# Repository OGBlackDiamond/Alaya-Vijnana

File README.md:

# Alaya-Vijnana
A wireless split ortholinear column-staggered keyboard that uses the Framework keyboard control board.

This is an adaptation of [Alaya-Vijnana-v2](https://github.com/OGBlackDiamond/Alaya-Vijnana-v2) to use Framework's wireless keyboard hardware, made under their developer program.

## What's an Alaya Vijnana?
The Alaya Vijnana system is a control interface to connect a Gundam pilot to their machine. I'm a nerd, and I name all of my computers after mobile suits (usually Gundams). Since a keyboard is how I interface with my computer, I felt a Gundam control system was an apt name.

For more information, visit [the IBO wiki](https://g-tekketsu.fandom.com/wiki/Alaya-Vijnana_System).

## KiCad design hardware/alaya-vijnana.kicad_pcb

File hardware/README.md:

# Alaya Vijnana Hardware

## B.O.M.
This is a complete B.O.M. for one half of the Alaya Vijnana's PCB components.

MCU:
* nRF52840 - [aQFN73](https://mm.digikey.com/Volume0/opasdata/d220001/medias/docus/6470/NRF52840-QFAA-F-R7.pdf)

Crystal Oscillators:
* 32MHz - [ECX-35B](https://ecsxtal.com/store/pdf/ecx_53b.pdf)
* 32.768kHz - [CM2012H](https://cfd.citizen.co.jp/cms/cfd/pdf/english/CM2012H_E.pdf)

Charger and Power:
* Charger - [BQ24075RGTR](https://www.digikey.com/en/products/detail/texas-instruments/BQ24075RGTR/2047273)
* Voltage Reg - [XC6220B331MR-G](https://www.digikey.com/en/products/detail/torex-semiconductor-ltd/XC6220B331MR-G/2138177?s=N4IgTCBcDaIB4GMBsYwAYBGBmLBGAtgE4gC6AvkA)

Battery Connector:
* JST PH - [S2B-PH-K-S](https://www.digikey.com/en/products/detail/jst-sales-america-inc/S2B-PH-K-S/926626)

Main to Cluster:
* 02x03 Header - 2 - [BHR-06-HUA](https://www.digikey.com/en/products/detail/adam-tech/BHR-06-HUA/10414833)
* Cable - 1 - [371](https://www.digikey.com/en/products/detail/adafruit-industries-llc/371/6827038)

Power Switch:
* E-Switch - [EG1224](https://www.digikey.com/en/products/detail/e-switch/EG1224/502052?s=N4IgTCBcDaIKIHEAEBGMYAsIC6BfIA)

USB-C Connector:
* USB CONN - [USB4085-GF-A](https://www.digikey.com/en/products/detail/gct/USB4085-GF-A/9859662?s=N4IgTCBcDaIKoGUBCAWADADgKwFoDiAYjgIIgC6AvkA)

Inductors:
* 10uH - 2 - [MLZ1608M100WTD25](https://www.digikey.com/en/products/detail/tdk-corporation/MLZ1608M100WTD25/4743176)
* 15nH - 1 - [LRC0603CJ15NGV001T](https://www.digikey.com/en/products/detail/johanson-technology-inc/LRC0603CJ15NGV001T/1561308)
* 4.7nH - 1 - [LRC0603CS4N7GV001T](https://www.digikey.com/en/products/detail/johanson-technology-inc/LRC0603CS4N7GV001T/1561296)

LEDs:
* Charge - 1 - [HSMD-C150](https://www.digikey.com/en/products/detail/broadcom-limited/HSMD-C150/637702)

Diodes:
* 21 - [CDSU101A](https://www.digikey.com/en/products/detail/comchip-technology/CDSU101A/1121034)

Hot Swap Sockets:
* 2 (1 = 20pc) - [4958](https://www.digikey.com/en/products/detail/adafruit-industries-llc/4958/13997772)

Resistors:
* 10k - 3 - [RC0603FR-0710KL](https://www.digikey.com/en/products/detail/yageo/RC0603FR-0710KL/726880)
* 10M - 1 - [RC0603JR-0710ML](https://www.digikey.com/en/products/detail/yageo/RC0603JR-0710ML/726701)
* 5.1k - 2 - [RC0603FR-075K1L](https://www.digikey.com/en/products/detail/yageo/RC0603FR-075K1L/727268)
* 2k - 1 - [RC0603JR-072KL](https://www.digikey.com/en/products/detail/yageo/RC0603JR-072KL/726726https://www.digikey.com/en/products/detail/yageo/RC0603JR-072KL/726726)

Capacitors:
* 12pF - 4 - [0603N120J500CT](https://www.digikey.com/en/products/detail/walsin-technology-corporation/0603N120J500CT/9355484)
* 1uF - 3 - [TMK107B7105KA-T](https://www.digikey.com/en/products/detail/taiyo-yuden/TMK107B7105KA-T/2714162)
* 4.7uF - 8 - [C1608X5R1C475K080AC](https://www.digikey.com/en/products/detail/tdk-corporation/C1608X5R1C475K080AC/2732913)
* 0.8pF - 1 - [CC0603BRNPO9BNR80](https://www.digikey.com/en/products/detail/yageo/CC0603BRNPO9BNR80/11490491)
* 0.5pF - 1 - [CBR06C508B5GAC](https://www.digikey.com/en/products/detail/kemet/CBR06C508B5GAC/3473906)
* 10uF - 1 - [LMK107BBJ106MALT](https://www.digikey.com/en/products/detail/taiyo-yuden/LMK107BBJ106MALT/3662195)
* 100pF - 2 - [CC0603JRNPO9BN101](https://www.digikey.com/en/products/detail/yageo/CC0603JRNPO9BN101/302803)
* 820pF - 1 - [CC0603KRX7R9BB821](https://www.digikey.com/en/products/detail/yageo/CC0603KRX7R9BB821/372862)
* 0.047uF - 1 - [CC0603KRX7R8BB473](https://www.digikey.com/en/products/detail/yageo/CC0603KRX7R8BB473/2103111)
* 0.1uF - 3 - [CC0603KRX7R7BB104](https://www.digikey.com/en/products/detail/yageo/CC0603KRX7R7BB104/302822)

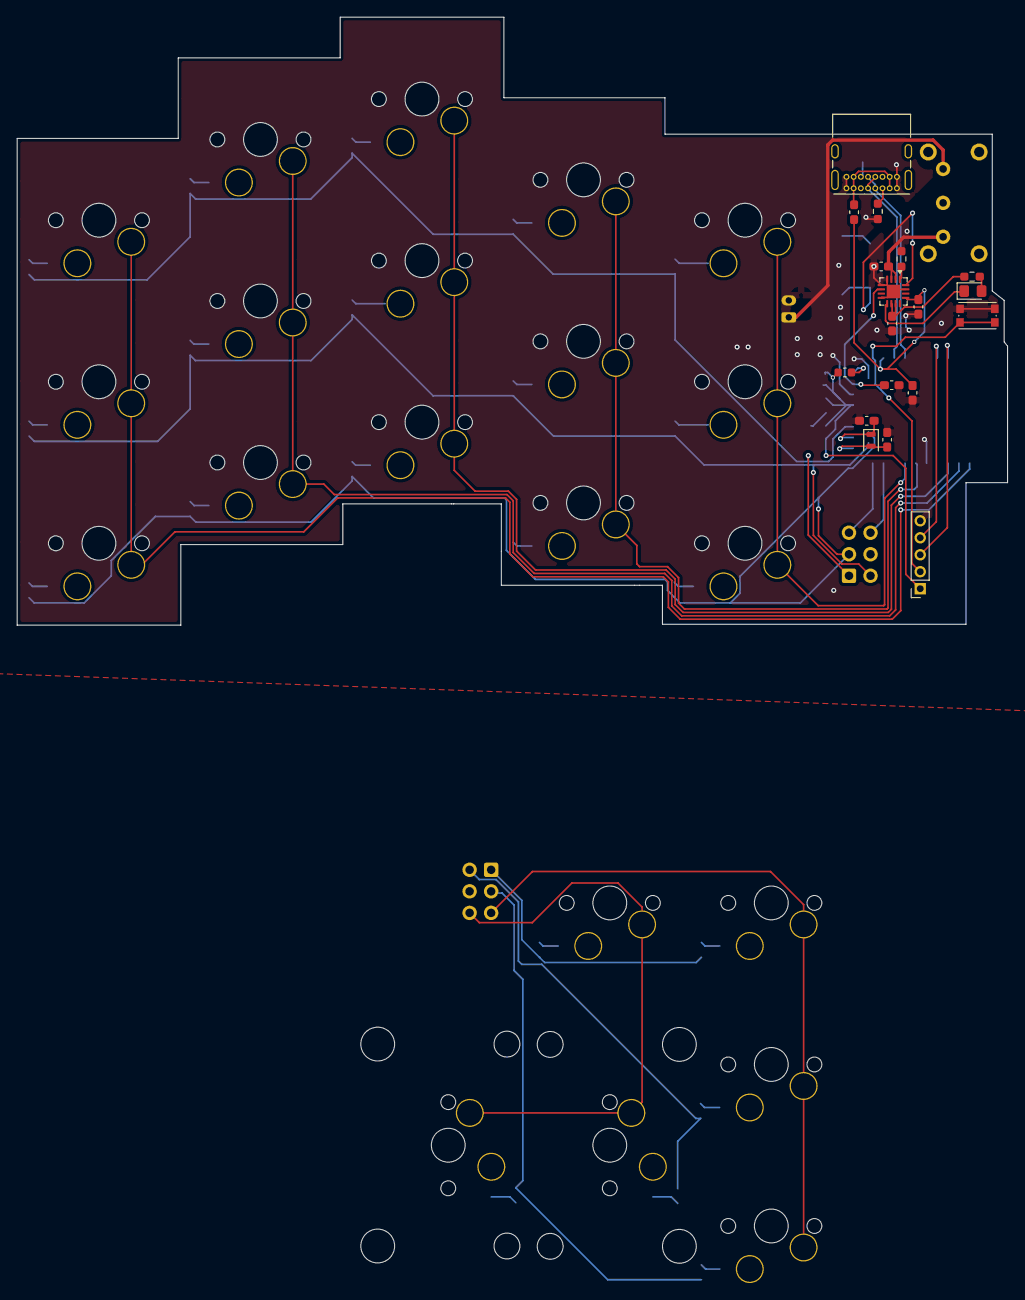
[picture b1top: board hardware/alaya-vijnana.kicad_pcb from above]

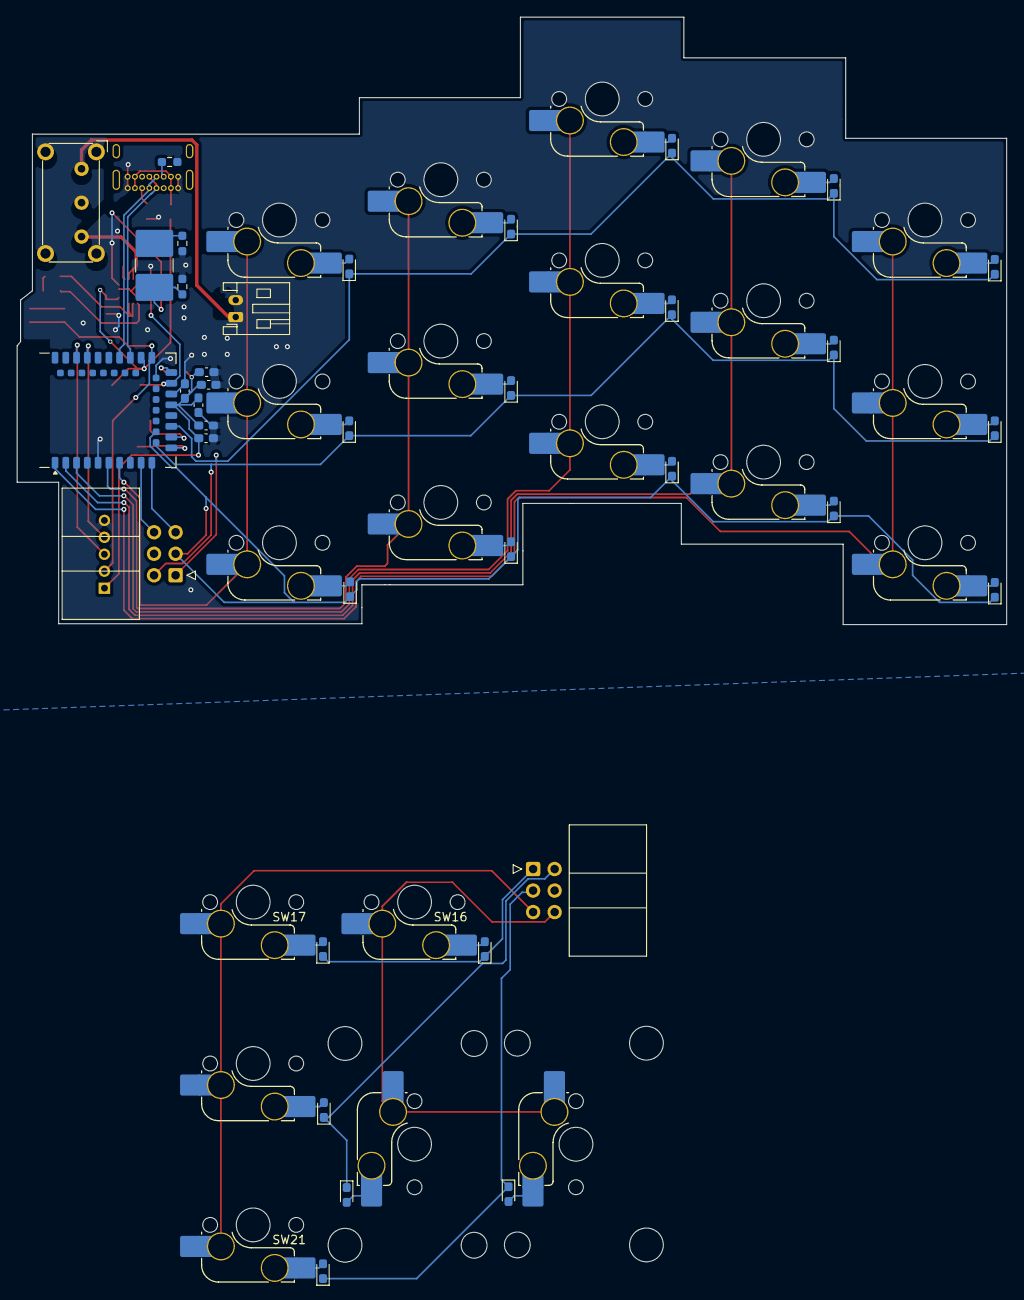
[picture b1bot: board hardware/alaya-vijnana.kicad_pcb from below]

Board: 2 copper layers, 116.8 x 71.7 mm, 75 parts (57 on the bottom side), 58 nets.

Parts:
C1, C30, C37, C46, C47: 4.7uF; C_0603_1608Metric_Pad1.08x0.95mm_HandSolder
C2: 1u; C_0603_1608Metric_Pad1.08x0.95mm_HandSolder
C26: 1uf; C_0603_1608Metric_Pad1.08x0.95mm_HandSolder
C27, C28, C29: 100nF; C_0603_1608Metric_Pad1.08x0.95mm_HandSolder
C41, C42: 12pF; C_0603_1608Metric_Pad1.08x0.95mm_HandSolder
C44: 1uF; C_0603_1608Metric_Pad1.08x0.95mm_HandSolder
D22, D23, D24, D25, D26, D27, D28, D29, D30, D31, D32, D33, D34, D35, D36, D37, D38, D39, D40, D41, D42: D; D_0603_1608Metric_Pad1.05x0.95mm_HandSolder
F1: 750 mA; Fuse_0603_1608Metric_Pad1.05x0.95mm_HandSolder
J1: Debug/Flash; PinSocket_1x05_P2.00mm_Vertical
J3: Bat; JST_PH_S2B-PH-K_1x02_P2.00mm_Horizontal
J4: USB_C_Receptacle_USB2.0_16P; USB_C_Receptacle_GCT_USB4085
J6: MAIN_CONN; IDC-Header_2x03_P2.54mm_Horizontal
J7: CLUSTER_CONN; IDC-Header_2x03_P2.54mm_Horizontal
L7: 10uH; L_0603_1608Metric
LED2: Charge_LED; LED_0805_2012Metric_Pad1.15x1.40mm_HandSolder
POWER-SW1: Power_Switch; SW_E-Switch_EG1224_SPDT_Angled
R8: 2k; R_0603_1608Metric_Pad0.98x0.95mm_HandSolder
R9, R11, R12: 10k; R_0603_1608Metric_Pad0.98x0.95mm_HandSolder
R13, R14: 5.1k; R_0603_1608Metric_Pad0.98x0.95mm_HandSolder
RESET-SW1: Reset; SW_Push_1P1T_NO_CK_KMR2
SW1, SW2, SW3, SW4, SW5, SW6, SW7, SW8, SW9, SW10, SW11, SW12, SW13, SW14, SW15, SW16, SW17, SW18, SW19, SW20, SW21: MX HotSwap; SW_MX_HS_CPG151101S11_1u
TP2: Charge Boost; R_2816_7142Metric_Pad3.20x4.45mm_HandSolder
U1: nRF52840_E73-2G4M08S1C
U6: BQ24075RGT; VQFN-16-1EP_3x3mm_P0.5mm_EP1.6x1.6mm
X2: 32.768kHz; Crystal_SMD_2012-2Pin_2.0x1.2mm

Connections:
BAT+: J3.1, POWER-SW1.1 (B)
BAT-: C1.1, C2.2, C26.2, C27.2, C28.2, C29.2, C30.2, C37.1, C41.1, C42.1, C44.1, C46.1, C47.2, J1.5, J3.2, J4.A1 (GND), J4.A12 (GND), J4.B1 (GND), J4.B12 (GND), R8.1, R9.2, R11.2, R13.2, R14.2, RESET-SW1.2, U1.5 (GND), U1.21 (GND), U1.24 (GND), U6.4 (~CE), U6.5 (EN2), U6.8 (VSS), U6.15 (SYSOFF), U6.17 (VSS)
COL0: SW1.1, SW6.1, SW11.1, U1.1 (P1.11)
COL1: SW2.1, SW7.1, SW12.1, U1.2 (P1.10)
COL2: SW3.1, SW8.1, SW13.1, U1.3 (P0.03/AIN1)
COL3: SW4.1, SW9.1, SW14.1, U1.6 (P1.13)
COL4: SW5.1, SW10.1, SW15.1, U1.7 (P0.02/AIN0)
COL5: J6.6, U1.9 (P0.31/AIN7)
COL6: J6.5, U1.10 (P0.30/AIN6)
C_COL5: J7.6, SW16.1, SW18.1, SW20.1
C_COL6: J7.5, SW17.1, SW19.1, SW21.1
C_ROW0: D37.1 (K), D40.1 (K), J7.1
C_ROW1: D38.1 (K), D41.1 (K), J7.2
C_ROW2: D39.1 (K), D42.1 (K), J7.3
D+: J4.A6 (D+), J4.B6 (D+), U1.31 (D+)
D-: J4.A7 (D-), J4.B7 (D-), U1.29 (D-)
unnamed: D22.2 (A), SW1.2
unnamed: D23.2 (A), SW6.2
unnamed: D24.2 (A), SW11.2
unnamed: D25.2 (A), SW2.2
unnamed: D26.2 (A), SW7.2
unnamed: D27.2 (A), SW12.2
unnamed: D28.2 (A), SW3.2
unnamed: D29.2 (A), SW8.2
unnamed: D30.2 (A), SW13.2
unnamed: D31.2 (A), SW4.2
unnamed: D32.2 (A), SW9.2
unnamed: D33.2 (A), SW14.2
unnamed: D34.2 (A), SW5.2
unnamed: D35.2 (A), SW10.2
unnamed: D36.2 (A), SW15.2
unnamed: D37.2 (A), SW16.2
unnamed: D38.2 (A), SW18.2
unnamed: D39.2 (A), SW20.2
unnamed: D40.2 (A), SW17.2
unnamed: D41.2 (A), SW19.2
unnamed: D42.2 (A), SW21.2
unnamed: F1.1, J4.A4 (VBUS), J4.A9 (VBUS), J4.B4 (VBUS), J4.B9 (VBUS)
unnamed: J4.A5 (CC1), R13.1
unnamed: J4.B5 (CC2), R14.1
unnamed: LED2.2 (A), R12.1
unnamed: LED2.1 (K), U6.9 (~CHG)
unnamed: R8.2, TP2.2
unnamed: L7.1, U1.25 (DCCH)
unnamed: C41.2, U1.11 (P0.00/XL1), X2.2
unnamed: C42.2, U1.13 (P0.01/XL2), X2.1
unnamed: R9.1, TP2.1, U6.16 (ISET)
unnamed: R11.1, U6.1 (TS)
RESET: J1.2, RESET-SW1.1, U1.26 (P0.18/~RESET)
ROW0: D22.1 (K), D25.1 (K), D28.1 (K), D31.1 (K), D34.1 (K), J6.1, U1.15 (P0.05/AIN3)
ROW1: D23.1 (K), D26.1 (K), D29.1 (K), D32.1 (K), D35.1 (K), J6.2, U1.12 (P0.26)
ROW2: D24.1 (K), D27.1 (K), D30.1 (K), D33.1 (K), D36.1 (K), J6.3, U1.14 (P0.06)
SWDCLK: J1.3, U1.39 (SWDCLK)
SWDIO: J1.4, U1.37 (SWDIO)
VBAT: C47.1, POWER-SW1.3 (A), U6.2 (BAT), U6.3 (BAT)
VBUS: C1.2, C44.2, F1.2, U1.27 (VBUS), U6.13 (IN)
VDDH: C37.2, C46.2, R12.2, U1.23 (VDDH), U6.6 (EN1), U6.10 (OUT), U6.11 (OUT)
VDD_NRF: C2.1, C26.1, C27.1, C28.1, C29.1, C30.1, J1.1, L7.2, U1.19 (VDD)

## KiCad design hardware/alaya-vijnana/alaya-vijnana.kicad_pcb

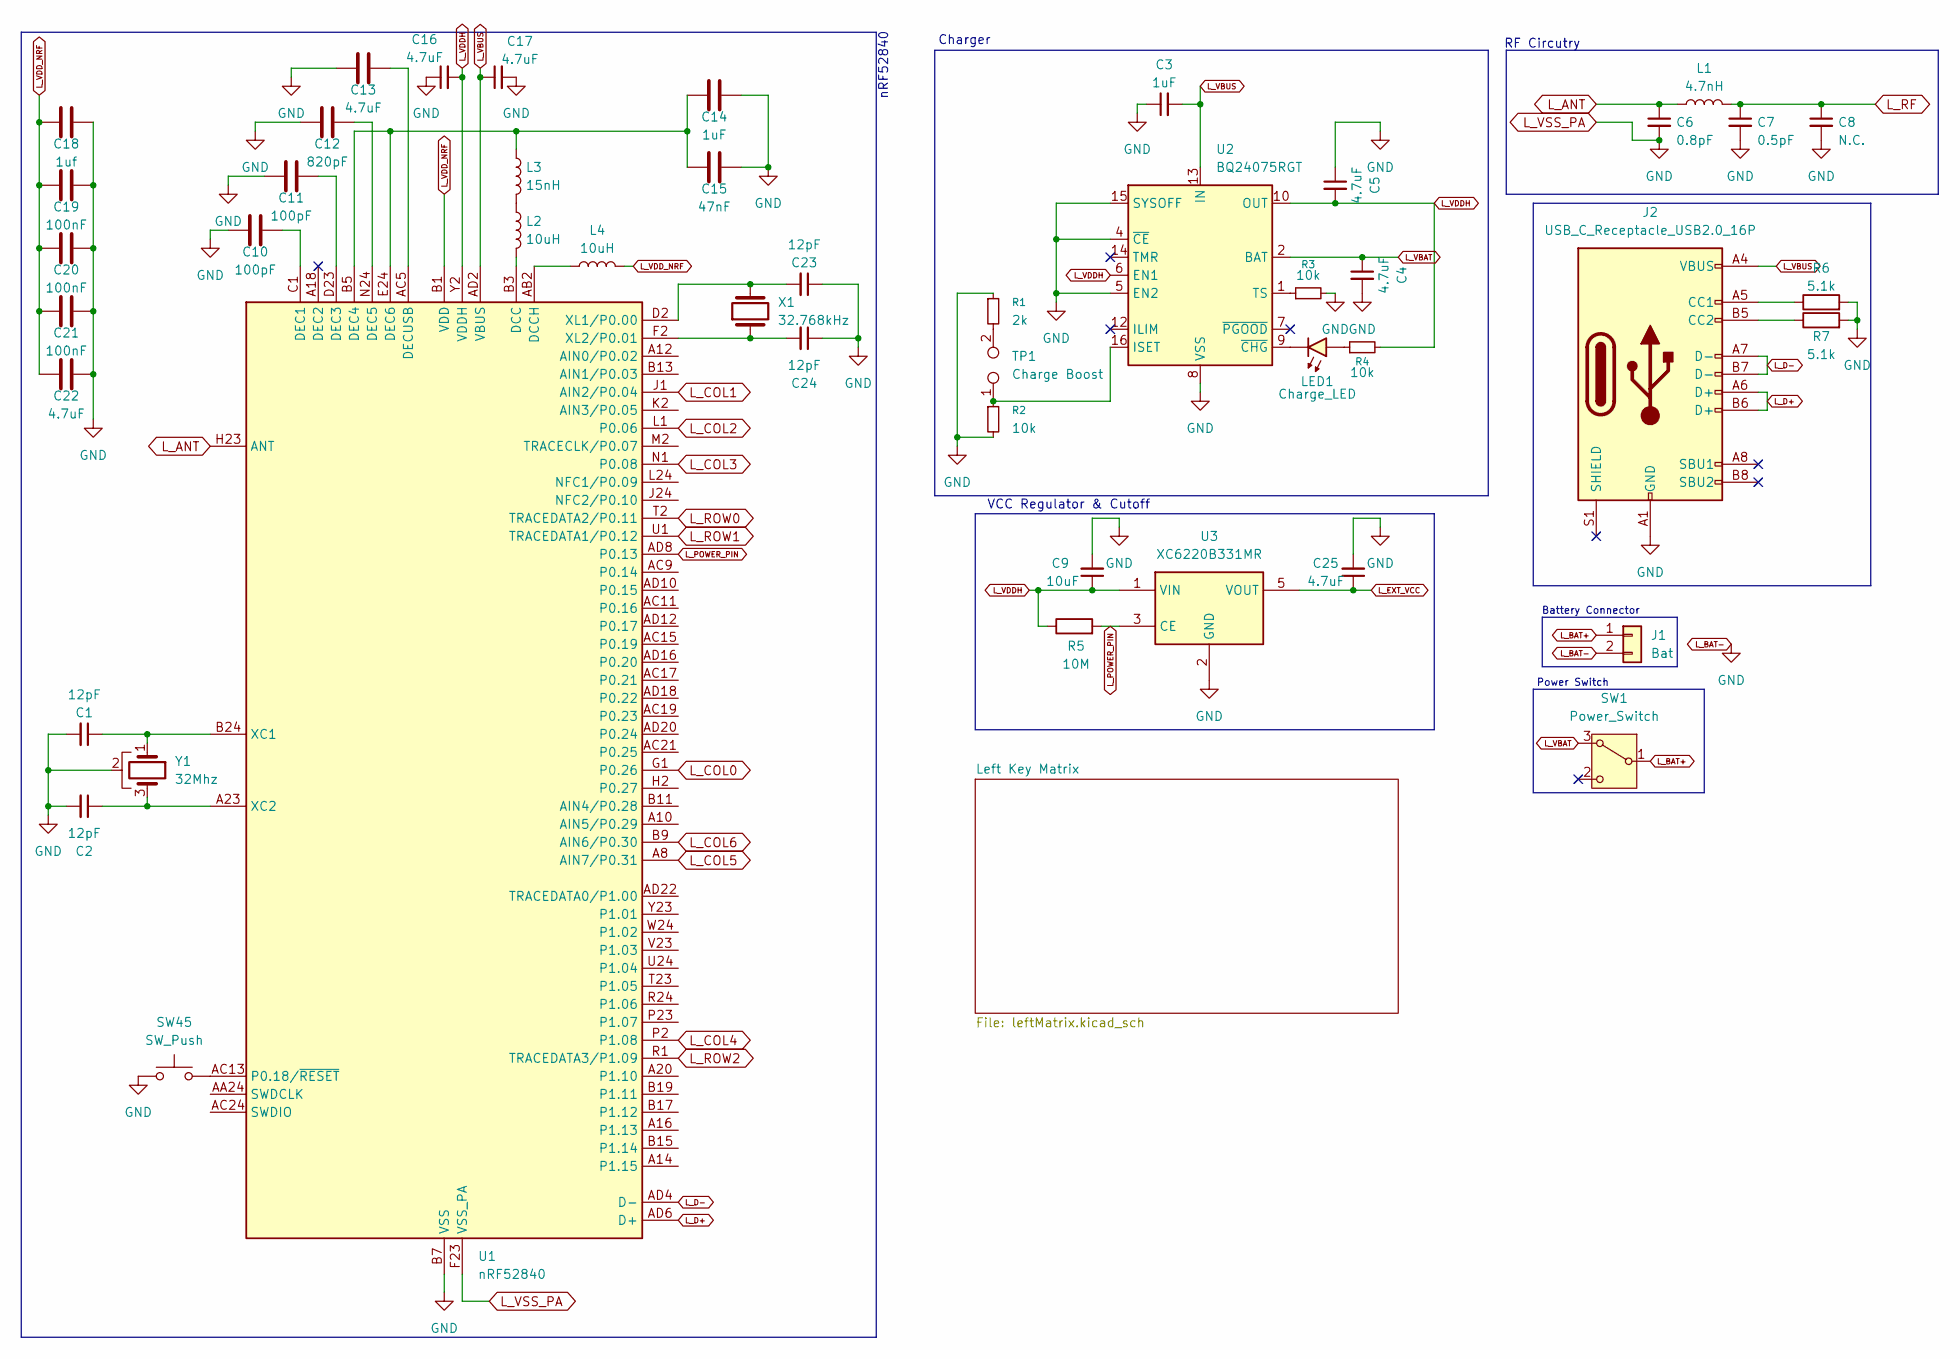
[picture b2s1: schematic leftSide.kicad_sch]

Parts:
C1, C2, C23, C24: 12pF; C_0603_1608Metric_Pad1.08x0.95mm_HandSolder
C3, C14: 1uF; C_0603_1608Metric_Pad1.08x0.95mm_HandSolder
C4, C5, C13, C16, C17, C22, C25: 4.7uF; C_0603_1608Metric_Pad1.08x0.95mm_HandSolder
C6: 0.8pF; C_0603_1608Metric_Pad1.08x0.95mm_HandSolder
C7: 0.5pF; C_0603_1608Metric_Pad1.08x0.95mm_HandSolder
C8: N.C.; C_0603_1608Metric_Pad1.08x0.95mm_HandSolder
C9: 10uF; C_0603_1608Metric_Pad1.08x0.95mm_HandSolder
C10, C11: 100pF; C_0603_1608Metric_Pad1.08x0.95mm_HandSolder
C12: 820pF; C_0603_1608Metric_Pad1.08x0.95mm_HandSolder
C15: 47nF; C_0603_1608Metric_Pad1.08x0.95mm_HandSolder
C18: 1uf; C_0603_1608Metric_Pad1.08x0.95mm_HandSolder
C19, C20, C21: 100nF; C_0603_1608Metric_Pad1.08x0.95mm_HandSolder
J1: Bat; JST_PH_S2B-PH-K_1x02_P2.00mm_Horizontal
J2: USB_C_Receptacle_USB2.0_16P; USB_C_Receptacle_GCT_USB4085
L1: 4.7nH; L_0402_1005Metric_Pad0.77x0.64mm_HandSolder
L2, L4: 10uH; L_0603_1608Metric
L3: 15nH; L_0603_1608Metric
LED1: Charge_LED; LED_1206_3216Metric
R1: 2k; R_0603_1608Metric_Pad0.98x0.95mm_HandSolder
R2, R3, R4: 10k; R_0603_1608Metric_Pad0.98x0.95mm_HandSolder
R5: 10M; R_0603_1608Metric_Pad0.98x0.95mm_HandSolder
R6, R7: 5.1k; R_0603_1608Metric_Pad0.98x0.95mm_HandSolder
SW1: Power_Switch; SW_E-Switch_EG1224_SPDT_Angled
SW45: SW_Push; SW_Push_1P1T_NO_CK_KMR2
TP1: Charge Boost; R_2816_7142Metric_Pad3.20x4.45mm_HandSolder
U1: nRF52840; Nordic_AQFN-73-1EP_7x7mm_P0.5mm
U2: BQ24075RGT; VQFN-16-1EP_3x3mm_P0.5mm_EP1.6x1.6mm
U3: XC6220B331MR; SOT-23-5
X1: 32.768kHz; Crystal_SMD_2012-2Pin_2.0x1.2mm
Y1: 32Mhz; Crystal_SMD_3225-4Pin_3.2x2.5mm_HandSoldering

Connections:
L_ANT: C6.1, L1.1, U1.H23 (ANT)
L_BAT+: J1.1, SW1.1 (B)
L_BAT-: C1.2, C2.2, C3.1, C4.2, C5.1, C6.2, C7.2, C8.2, C9.2, C10.1, C11.1, C12.1, C13.1, C14.2, C15.2, C16.1, C17.2, C18.2, C19.2, C20.2, C21.2, C22.2, C23.1, C24.1, C25.2, J1.2, J2.A1 (GND), J2.A12 (GND), J2.B1 (GND), J2.B12 (GND), R1.1, R2.2, R3.2, R6.2, R7.2, SW45.1, U1.B7 (VSS), U1.EP (VSS), U1.F23 (VSS_PA), U2.4 (~CE), U2.5 (EN2), U2.8 (VSS), U2.15 (SYSOFF), U2.17 (VSS), U3.2 (GND), Y1.2; also elsewhere on the board
L_COL0: U1.G1 (P0.26); also elsewhere on the board
L_COL1: U1.J1 (AIN2/P0.04); also elsewhere on the board
L_COL2: U1.L1 (P0.06); also elsewhere on the board
L_COL3: U1.N1 (P0.08); also elsewhere on the board
L_COL4: U1.P2 (P1.08); also elsewhere on the board
L_COL5: U1.A8 (AIN7/P0.31); also elsewhere on the board
L_COL6: U1.B9 (AIN6/P0.30); also elsewhere on the board
L_D+: J2.A6 (D+), J2.B6 (D+), U1.AD6 (D+)
L_D-: J2.A7 (D-), J2.B7 (D-), U1.AD4 (D-)
L_EXT_VCC: C25.1, U3.5 (VOUT)
L_POWER_PIN: R5.2, U1.AD8 (P0.13), U3.3 (CE)
L_RF: C7.1, C8.1, L1.2
L_ROW0: U1.T2 (TRACEDATA2/P0.11); also elsewhere on the board
L_ROW1: U1.U1 (TRACEDATA1/P0.12); also elsewhere on the board
L_ROW2: U1.R1 (TRACEDATA3/P1.09); also elsewhere on the board
L_VBAT: C4.1, SW1.3 (A), U2.2 (BAT), U2.3 (BAT)
L_VBUS: C3.2, C17.1, J2.A4 (VBUS), J2.A9 (VBUS), J2.B4 (VBUS), J2.B9 (VBUS), U1.AD2 (VBUS), U2.13 (IN)
L_VDDH: C5.2, C9.1, C16.2, R4.2, R5.1, U1.Y2 (VDDH), U2.6 (EN1), U2.10 (OUT), U2.11 (OUT), U3.1 (VIN)
L_VDD_NRF: C18.1, C19.1, C20.1, C21.1, C22.1, L4.2, U1.A22 (VDD), U1.AD14 (VDD), U1.AD23 (VDD), U1.B1 (VDD), U1.W1 (VDD)
unnamed: J2.A5 (CC1), R6.1
unnamed: J2.B5 (CC2), R7.1
unnamed: L2.1, L3.2
unnamed: LED1.2 (A), R4.1
unnamed: LED1.1 (K), U2.9 (~CHG)
unnamed: R1.2, TP1.2
unnamed: L2.2, U1.B3 (DCC)
unnamed: L4.1, U1.AB2 (DCCH)
unnamed: C10.2, U1.C1 (DEC1)
unnamed: C11.2, U1.D23 (DEC3)
unnamed: C14.1, C15.1, L3.1, U1.B5 (DEC4), U1.E24 (DEC6)
unnamed: C12.2, U1.N24 (DEC5)
unnamed: C13.2, U1.AC5 (DECUSB)
unnamed: SW45.2, U1.AC13 (P0.18/~RESET)
unnamed: C1.1, U1.B24 (XC1), Y1.1
unnamed: C2.1, U1.A23 (XC2), Y1.3
unnamed: C23.2, U1.D2 (XL1/P0.00), X1.2
unnamed: C24.2, U1.F2 (XL2/P0.01), X1.1
unnamed: R2.1, TP1.1, U2.16 (ISET)
unnamed: R3.1, U2.1 (TS)

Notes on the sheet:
Charger
nRF52840
RF Circutry
Power Switch
VCC Regulator & Cutoff
Battery Connector

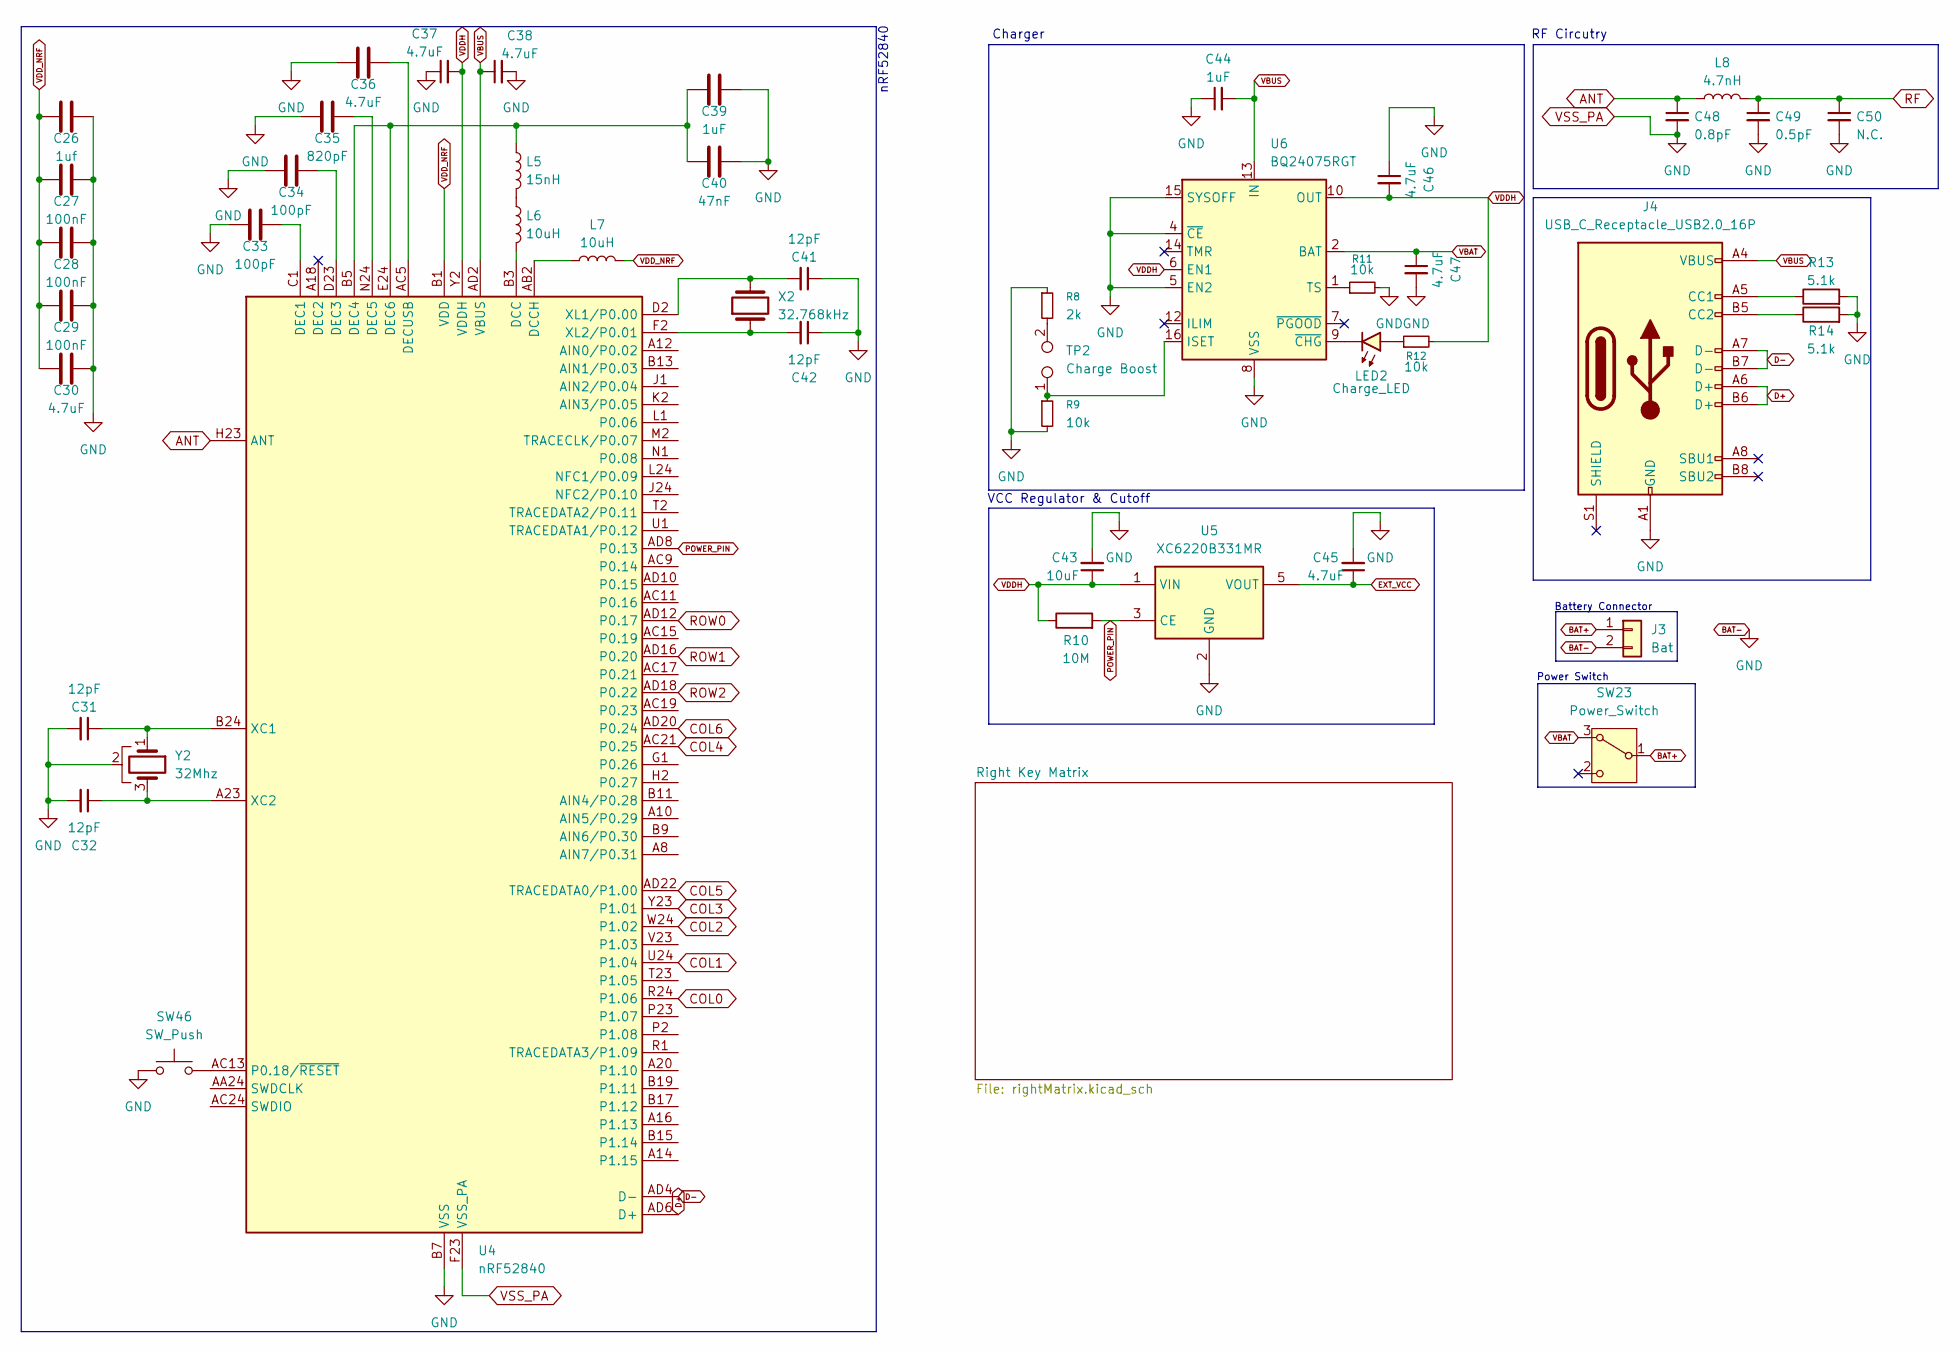
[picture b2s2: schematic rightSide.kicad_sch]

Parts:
C26: 1uf; C_0603_1608Metric_Pad1.08x0.95mm_HandSolder
C27, C28, C29: 100nF; C_0603_1608Metric_Pad1.08x0.95mm_HandSolder
C30, C36, C37, C38, C45, C46, C47: 4.7uF; C_0603_1608Metric_Pad1.08x0.95mm_HandSolder
C31, C32, C41, C42: 12pF; C_0603_1608Metric_Pad1.08x0.95mm_HandSolder
C33, C34: 100pF; C_0603_1608Metric_Pad1.08x0.95mm_HandSolder
C35: 820pF; C_0603_1608Metric_Pad1.08x0.95mm_HandSolder
C39, C44: 1uF; C_0603_1608Metric_Pad1.08x0.95mm_HandSolder
C40: 47nF; C_0603_1608Metric_Pad1.08x0.95mm_HandSolder
C43: 10uF; C_0603_1608Metric_Pad1.08x0.95mm_HandSolder
C48: 0.8pF; C_0603_1608Metric_Pad1.08x0.95mm_HandSolder
C49: 0.5pF; C_0603_1608Metric_Pad1.08x0.95mm_HandSolder
C50: N.C.; C_0603_1608Metric_Pad1.08x0.95mm_HandSolder
J3: Bat; JST_PH_S2B-PH-K_1x02_P2.00mm_Horizontal
J4: USB_C_Receptacle_USB2.0_16P; USB_C_Receptacle_GCT_USB4085
L5: 15nH; L_0603_1608Metric
L6, L7: 10uH; L_0603_1608Metric
L8: 4.7nH; L_0402_1005Metric_Pad0.77x0.64mm_HandSolder
LED2: Charge_LED; LED_1206_3216Metric
R8: 2k; R_0603_1608Metric_Pad0.98x0.95mm_HandSolder
R9, R11, R12: 10k; R_0603_1608Metric_Pad0.98x0.95mm_HandSolder
R10: 10M; R_0603_1608Metric_Pad0.98x0.95mm_HandSolder
R13, R14: 5.1k; R_0603_1608Metric_Pad0.98x0.95mm_HandSolder
SW23: Power_Switch; SW_E-Switch_EG1224_SPDT_Angled
SW46: SW_Push; SW_Push_1P1T_NO_CK_KMR2
TP2: Charge Boost; R_2816_7142Metric_Pad3.20x4.45mm_HandSolder
U4: nRF52840; Nordic_AQFN-73-1EP_7x7mm_P0.5mm
U5: XC6220B331MR; SOT-23-5
U6: BQ24075RGT; VQFN-16-1EP_3x3mm_P0.5mm_EP1.6x1.6mm
X2: 32.768kHz; Crystal_SMD_2012-2Pin_2.0x1.2mm
Y2: 32Mhz; Crystal_SMD_3225-4Pin_3.2x2.5mm_HandSoldering

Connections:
ANT: C48.1, L8.1, U4.H23 (ANT)
BAT+: J3.1, SW23.1 (B)
COL0: U4.R24 (P1.06); also elsewhere on the board
COL1: U4.U24 (P1.04); also elsewhere on the board
COL2: U4.W24 (P1.02); also elsewhere on the board
COL3: U4.Y23 (P1.01); also elsewhere on the board
COL4: U4.AC21 (P0.25); also elsewhere on the board
COL5: U4.AD22 (TRACEDATA0/P1.00); also elsewhere on the board
COL6: U4.AD20 (P0.24); also elsewhere on the board
D+: J4.A6 (D+), J4.B6 (D+), U4.AD6 (D+)
D-: J4.A7 (D-), J4.B7 (D-), U4.AD4 (D-)
EXT_VCC: C45.1, U5.5 (VOUT)
L_BAT-: C26.2, C27.2, C28.2, C29.2, C30.2, C31.2, C32.2, C33.1, C34.1, C35.1, C36.1, C37.1, C38.2, C39.2, C40.2, C41.1, C42.1, C43.2, C44.1, C45.2, C46.1, C47.2, C48.2, C49.2, C50.2, J3.2, J4.A1 (GND), J4.A12 (GND), J4.B1 (GND), J4.B12 (GND), R8.1, R9.2, R11.2, R13.2, R14.2, SW46.1, U4.B7 (VSS), U4.EP (VSS), U4.F23 (VSS_PA), U5.2 (GND), U6.4 (~CE), U6.5 (EN2), U6.8 (VSS), U6.15 (SYSOFF), U6.17 (VSS), Y2.2; also elsewhere on the board
unnamed: J4.A5 (CC1), R13.1
unnamed: J4.B5 (CC2), R14.1
unnamed: L5.2, L6.1
unnamed: LED2.2 (A), R12.1
unnamed: LED2.1 (K), U6.9 (~CHG)
unnamed: R8.2, TP2.2
unnamed: L6.2, U4.B3 (DCC)
unnamed: L7.1, U4.AB2 (DCCH)
unnamed: C33.2, U4.C1 (DEC1)
unnamed: C34.2, U4.D23 (DEC3)
unnamed: C39.1, C40.1, L5.1, U4.B5 (DEC4), U4.E24 (DEC6)
unnamed: C35.2, U4.N24 (DEC5)
unnamed: C36.2, U4.AC5 (DECUSB)
unnamed: SW46.2, U4.AC13 (P0.18/~RESET)
unnamed: C31.1, U4.B24 (XC1), Y2.1
unnamed: C32.1, U4.A23 (XC2), Y2.3
unnamed: C41.2, U4.D2 (XL1/P0.00), X2.2
unnamed: C42.2, U4.F2 (XL2/P0.01), X2.1
unnamed: R9.1, TP2.1, U6.16 (ISET)
unnamed: R11.1, U6.1 (TS)
POWER_PIN: R10.2, U4.AD8 (P0.13), U5.3 (CE)
RF: C49.1, C50.1, L8.2
ROW0: U4.AD12 (P0.17); also elsewhere on the board
ROW1: U4.AD16 (P0.20); also elsewhere on the board
ROW2: U4.AD18 (P0.22); also elsewhere on the board
VBAT: C47.1, SW23.3 (A), U6.2 (BAT), U6.3 (BAT)
VBUS: C38.1, C44.2, J4.A4 (VBUS), J4.A9 (VBUS), J4.B4 (VBUS), J4.B9 (VBUS), U4.AD2 (VBUS), U6.13 (IN)
VDDH: C37.2, C43.1, C46.2, R10.1, R12.2, U4.Y2 (VDDH), U5.1 (VIN), U6.6 (EN1), U6.10 (OUT), U6.11 (OUT)
VDD_NRF: C26.1, C27.1, C28.1, C29.1, C30.1, L7.2, U4.A22 (VDD), U4.AD14 (VDD), U4.AD23 (VDD), U4.B1 (VDD), U4.W1 (VDD)

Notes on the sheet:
Charger
Battery Connector
VCC Regulator & Cutoff
Power Switch
nRF52840
RF Circutry

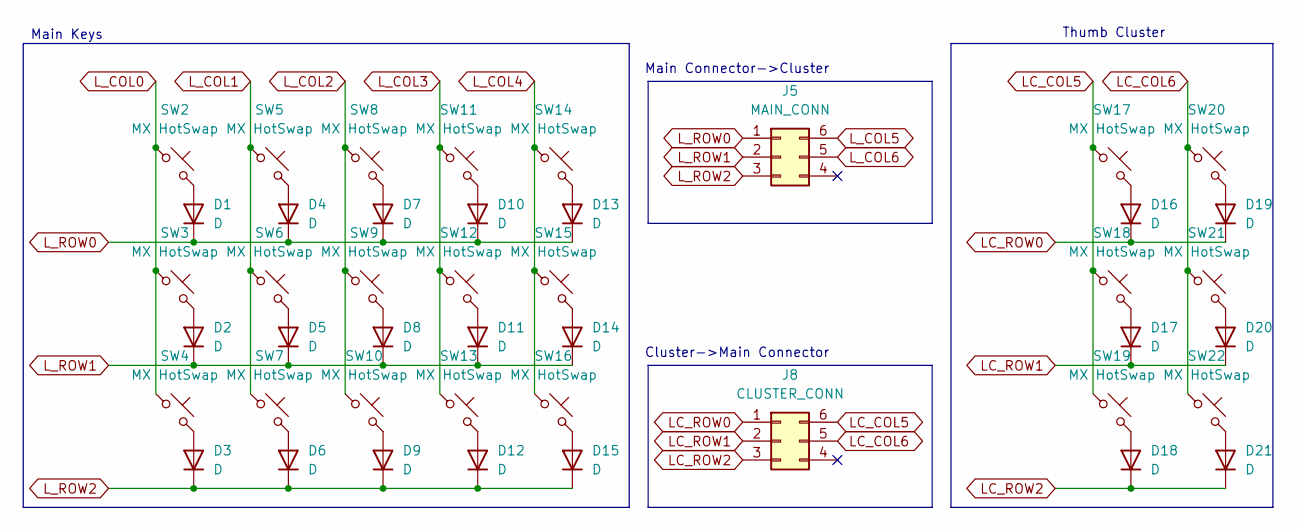
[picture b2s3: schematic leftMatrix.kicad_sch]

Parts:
D1, D2, D3, D4, D5, D6, D7, D8, D9, D10, D11, D12, D13, D14, D15, D16, D17, D18, D19, D20, D21: D; D_0603_1608Metric_Pad1.05x0.95mm_HandSolder
J5: MAIN_CONN; IDC-Header_2x03_P2.54mm_Horizontal
J8: CLUSTER_CONN; IDC-Header_2x03_P2.54mm_Horizontal
SW2, SW3, SW4, SW5, SW6, SW7, SW8, SW9, SW10, SW11, SW12, SW13, SW14, SW15, SW16, SW17, SW20, SW21, SW22: MX HotSwap; MX-Hotswap-1U
SW18, SW19: MX HotSwap; MX-Hotswap-2U

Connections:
LC_COL5: J8.6, SW17.1, SW18.1, SW19.1
LC_COL6: J8.5, SW20.1, SW21.1, SW22.1
LC_ROW0: D16.1 (K), D19.1 (K), J8.1
LC_ROW1: D17.1 (K), D20.1 (K), J8.2
LC_ROW2: D18.1 (K), D21.1 (K), J8.3
L_COL0: SW2.1, SW3.1, SW4.1; also elsewhere on the board
L_COL1: SW5.1, SW6.1, SW7.1; also elsewhere on the board
L_COL2: SW8.1, SW9.1, SW10.1; also elsewhere on the board
L_COL3: SW11.1, SW12.1, SW13.1; also elsewhere on the board
L_COL4: SW14.1, SW15.1, SW16.1; also elsewhere on the board
L_COL5: J5.6; also elsewhere on the board
L_COL6: J5.5; also elsewhere on the board
L_ROW0: D1.1 (K), D4.1 (K), D7.1 (K), D10.1 (K), D13.1 (K), J5.1; also elsewhere on the board
L_ROW1: D2.1 (K), D5.1 (K), D8.1 (K), D11.1 (K), D14.1 (K), J5.2; also elsewhere on the board
L_ROW2: D3.1 (K), D6.1 (K), D9.1 (K), D12.1 (K), D15.1 (K), J5.3; also elsewhere on the board
unnamed: D1.2 (A), SW2.2
unnamed: D2.2 (A), SW3.2
unnamed: D3.2 (A), SW4.2
unnamed: D4.2 (A), SW5.2
unnamed: D5.2 (A), SW6.2
unnamed: D6.2 (A), SW7.2
unnamed: D7.2 (A), SW8.2
unnamed: D8.2 (A), SW9.2
unnamed: D9.2 (A), SW10.2
unnamed: D10.2 (A), SW11.2
unnamed: D11.2 (A), SW12.2
unnamed: D12.2 (A), SW13.2
unnamed: D13.2 (A), SW14.2
unnamed: D14.2 (A), SW15.2
unnamed: D15.2 (A), SW16.2
unnamed: D16.2 (A), SW17.2
unnamed: D17.2 (A), SW18.2
unnamed: D18.2 (A), SW19.2
unnamed: D19.2 (A), SW20.2
unnamed: D20.2 (A), SW21.2
unnamed: D21.2 (A), SW22.2

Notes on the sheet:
Cluster->Main Connector
Thumb Cluster
Main Keys
Main Connector->Cluster

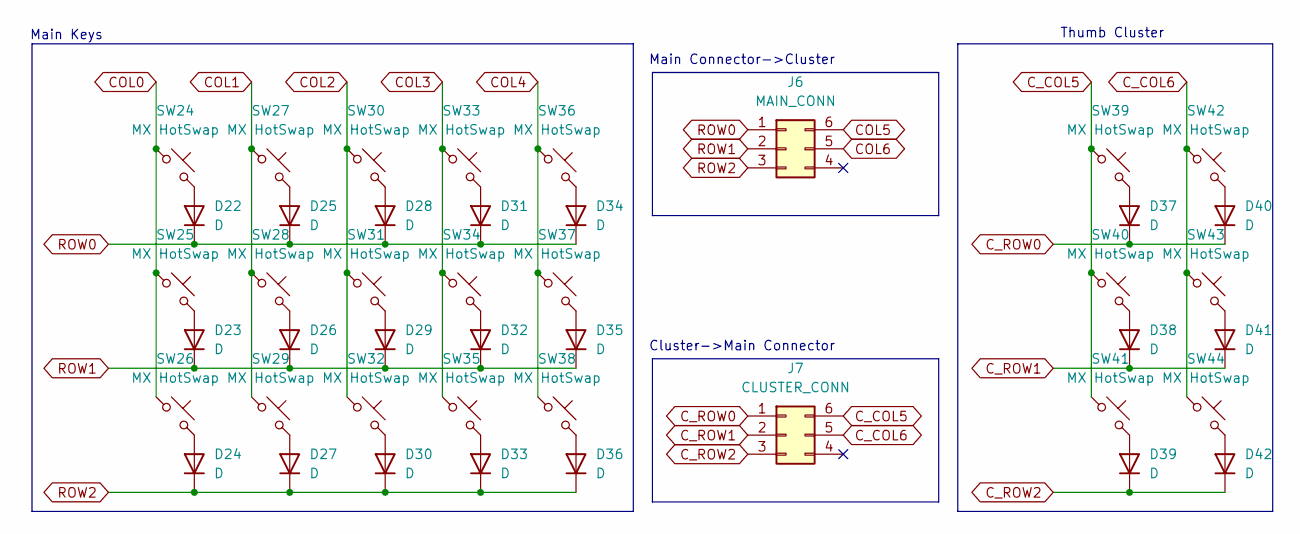
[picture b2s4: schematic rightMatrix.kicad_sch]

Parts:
D22, D23, D24, D25, D26, D27, D28, D29, D30, D31, D32, D33, D34, D35, D36, D37, D38, D39, D40, D41, D42: D; D_0603_1608Metric_Pad1.05x0.95mm_HandSolder
J6: MAIN_CONN; IDC-Header_2x03_P2.54mm_Horizontal
J7: CLUSTER_CONN; IDC-Header_2x03_P2.54mm_Horizontal
SW24, SW25, SW26, SW27, SW28, SW29, SW30, SW31, SW32, SW33, SW34, SW35, SW36, SW37, SW38, SW39, SW42, SW43, SW44: MX HotSwap; MX-Hotswap-1U
SW40, SW41: MX HotSwap; MX-Hotswap-2U

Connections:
COL0: SW24.1, SW25.1, SW26.1; also elsewhere on the board
COL1: SW27.1, SW28.1, SW29.1; also elsewhere on the board
COL2: SW30.1, SW31.1, SW32.1; also elsewhere on the board
COL3: SW33.1, SW34.1, SW35.1; also elsewhere on the board
COL4: SW36.1, SW37.1, SW38.1; also elsewhere on the board
COL5: J6.6; also elsewhere on the board
COL6: J6.5; also elsewhere on the board
C_COL5: J7.6, SW39.1, SW40.1, SW41.1
C_COL6: J7.5, SW42.1, SW43.1, SW44.1
C_ROW0: D37.1 (K), D40.1 (K), J7.1
C_ROW1: D38.1 (K), D41.1 (K), J7.2
C_ROW2: D39.1 (K), D42.1 (K), J7.3
unnamed: D22.2 (A), SW24.2
unnamed: D23.2 (A), SW25.2
unnamed: D24.2 (A), SW26.2
unnamed: D25.2 (A), SW27.2
unnamed: D26.2 (A), SW28.2
unnamed: D27.2 (A), SW29.2
unnamed: D28.2 (A), SW30.2
unnamed: D29.2 (A), SW31.2
unnamed: D30.2 (A), SW32.2
unnamed: D31.2 (A), SW33.2
unnamed: D32.2 (A), SW34.2
unnamed: D33.2 (A), SW35.2
unnamed: D34.2 (A), SW36.2
unnamed: D35.2 (A), SW37.2
unnamed: D36.2 (A), SW38.2
unnamed: D37.2 (A), SW39.2
unnamed: D38.2 (A), SW40.2
unnamed: D39.2 (A), SW41.2
unnamed: D40.2 (A), SW42.2
unnamed: D41.2 (A), SW43.2
unnamed: D42.2 (A), SW44.2
ROW0: D22.1 (K), D25.1 (K), D28.1 (K), D31.1 (K), D34.1 (K), J6.1; also elsewhere on the board
ROW1: D23.1 (K), D26.1 (K), D29.1 (K), D32.1 (K), D35.1 (K), J6.2; also elsewhere on the board
ROW2: D24.1 (K), D27.1 (K), D30.1 (K), D33.1 (K), D36.1 (K), J6.3; also elsewhere on the board

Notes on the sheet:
Main Keys
Cluster->Main Connector
Main Connector->Cluster
Thumb Cluster
